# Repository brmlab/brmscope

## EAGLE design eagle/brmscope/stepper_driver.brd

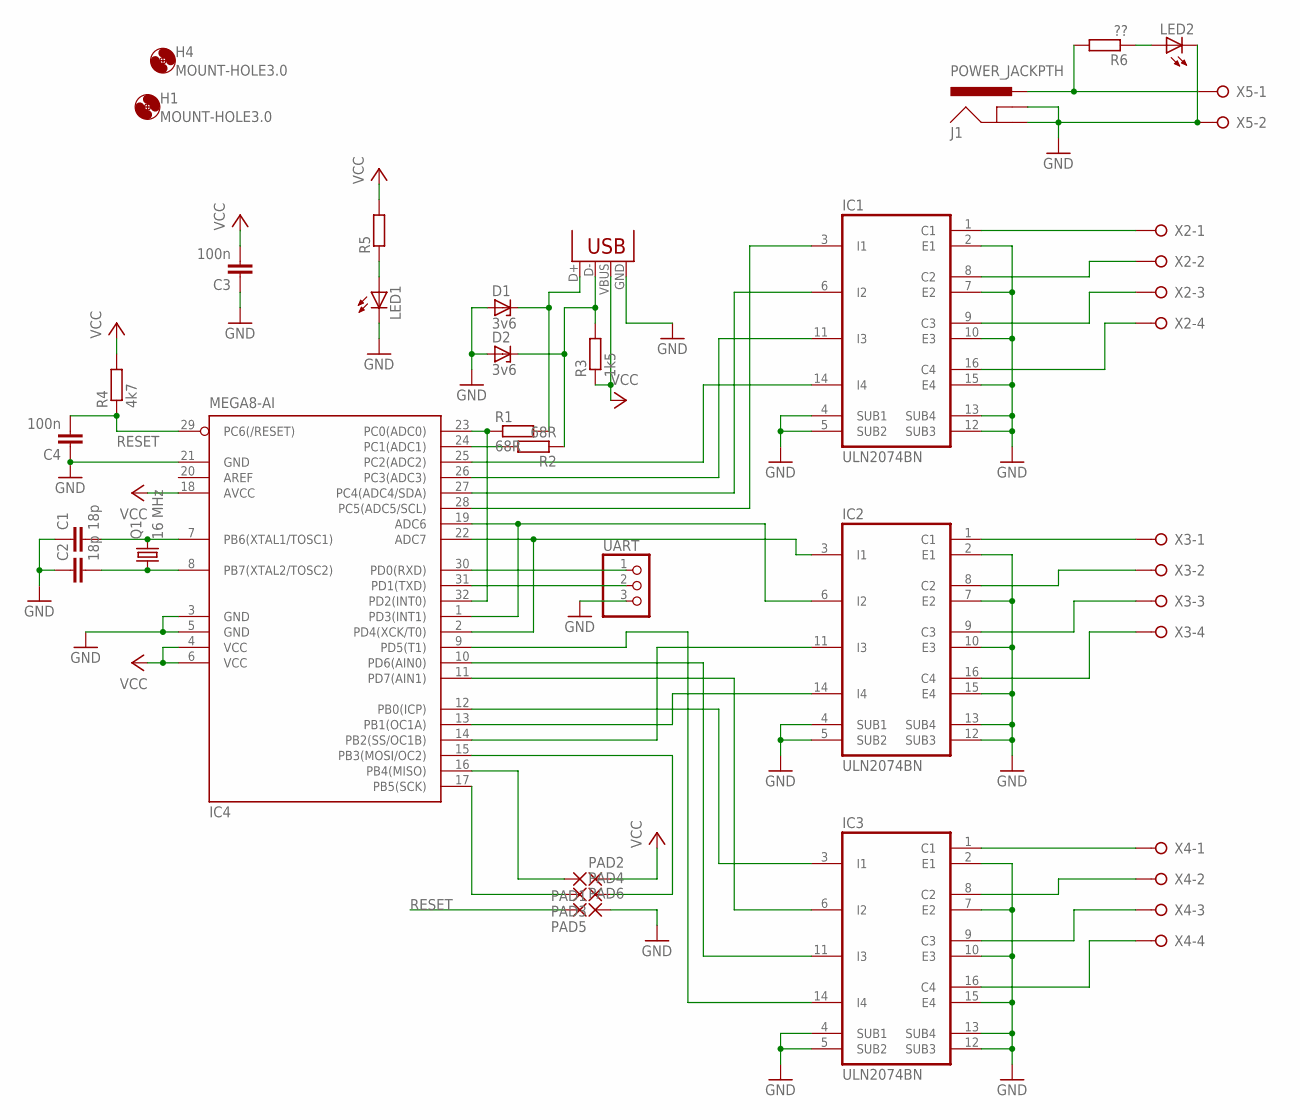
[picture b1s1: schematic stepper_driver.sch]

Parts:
C1, C2: 18p; C025-025X050
C3, C4: 100n; C025-025X050
D1, D2: 3v6; DO35Z10
H1, H4: MOUNT-HOLE3.0; 3,0
IC1, IC2, IC3: ULN2074BN; DIL16
IC4: MEGA8-AI; TQFP32-08
J1: POWER_JACKPTH; POWER_JACK_PTH
LED1, LED2: LED3MM
PAD1, PAD2, PAD3, PAD4, PAD5, PAD6: 2,15/1,0
Q1: 16 MHz; HC49/S
R1, R2: 68R; 0207/10
R3: 1k5; 0207/10
R4: 4k7; 0207/10
R5: R-EU_0207/10; 0207/10
R6: ??; 0207/10
UART: PINHD-1X3; 1X03
X1: USBPTH; USB-B-PTH
X2, X3, X4: W237-04P; W237-4P
X5: W237-02P; W237-132

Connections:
GND: C1.1, C2.1, C3.1, C4.1, D1.A, D2.A, IC1.2 (E1), IC1.4 (SUB1), IC1.5 (SUB2), IC1.7 (E2), IC1.10 (E3), IC1.12 (SUB3), IC1.13 (SUB4), IC1.15 (E4), IC2.2 (E1), IC2.4 (SUB1), IC2.5 (SUB2), IC2.7 (E2), IC2.10 (E3), IC2.12 (SUB3), IC2.13 (SUB4), IC2.15 (E4), IC3.2 (E1), IC3.4 (SUB1), IC3.5 (SUB2), IC3.7 (E2), IC3.10 (E3), IC3.12 (SUB3), IC3.13 (SUB4), IC3.15 (E4), IC4.3 (GND), IC4.5 (GND), IC4.21 (GND), J1.GND, J1.GNDBREAK, LED1.K (C), LED2.K (C), PAD6.1, UART.3, X1.GND, X5.2
unnamed: C2.2, IC4.8 (PB7(XTAL2/TOSC2)), Q1.1
unnamed: C1.2, IC4.7 (PB6(XTAL1/TOSC1)), Q1.2
unnamed: IC4.15 (PB3(MOSI/OC2)), PAD4.1
unnamed: IC4.23 (PC0(ADC0)), IC4.32 (PD2(INT0)), R1.1
unnamed: IC4.24 (PC1(ADC1)), R2.2
unnamed: D1.C, R1.2, X1.D+
unnamed: D2.C, R2.1, R3.2, X1.D-
unnamed: IC1.14 (I4), IC4.25 (PC2(ADC2))
unnamed: IC1.11 (I3), IC4.26 (PC3(ADC3))
unnamed: IC1.6 (I2), IC4.27 (PC4(ADC4/SDA))
unnamed: IC1.3 (I1), IC4.28 (PC5(ADC5/SCL))
unnamed: IC2.6 (I2), IC4.1 (PD3(INT1)), IC4.19 (ADC6)
unnamed: IC2.3 (I1), IC4.2 (PD4(XCK/T0)), IC4.22 (ADC7)
unnamed: IC4.17 (PB5(SCK)), PAD3.1
unnamed: IC4.16 (PB4(MISO)), PAD1.1
unnamed: IC2.11 (I3), IC4.14 (PB2(SS/OC1B))
unnamed: IC2.14 (I4), IC4.13 (PB1(OC1A))
unnamed: IC3.3 (I1), IC4.12 (PB0(ICP))
unnamed: IC3.6 (I2), IC4.11 (PD7(AIN1))
unnamed: IC3.14 (I4), IC4.9 (PD5(T1))
unnamed: IC3.11 (I3), IC4.10 (PD6(AIN0))
unnamed: IC4.30 (PD0(RXD)), UART.1
unnamed: IC4.31 (PD1(TXD)), UART.2
unnamed: IC1.1 (C1), X2.1
unnamed: IC1.8 (C2), X2.2
unnamed: IC1.9 (C3), X2.3
unnamed: IC1.16 (C4), X2.4
unnamed: IC2.1 (C1), X3.1
unnamed: IC2.8 (C2), X3.2
unnamed: IC2.9 (C3), X3.3
unnamed: IC2.16 (C4), X3.4
unnamed: IC3.1 (C1), X4.1
unnamed: IC3.8 (C2), X4.2
unnamed: IC3.9 (C3), X4.3
unnamed: IC3.16 (C4), X4.4
unnamed: LED1.A, R5.1
unnamed: J1.PWR, R6.2, X5.1
unnamed: LED2.A, R6.1
RESET: C4.2, IC4.29 (PC6(/RESET)), PAD5.1, R4.1
VCC: C3.2, IC4.4 (VCC), IC4.6 (VCC), IC4.18 (AVCC), PAD2.1, R3.1, R4.2, R5.2, X1.VBUS

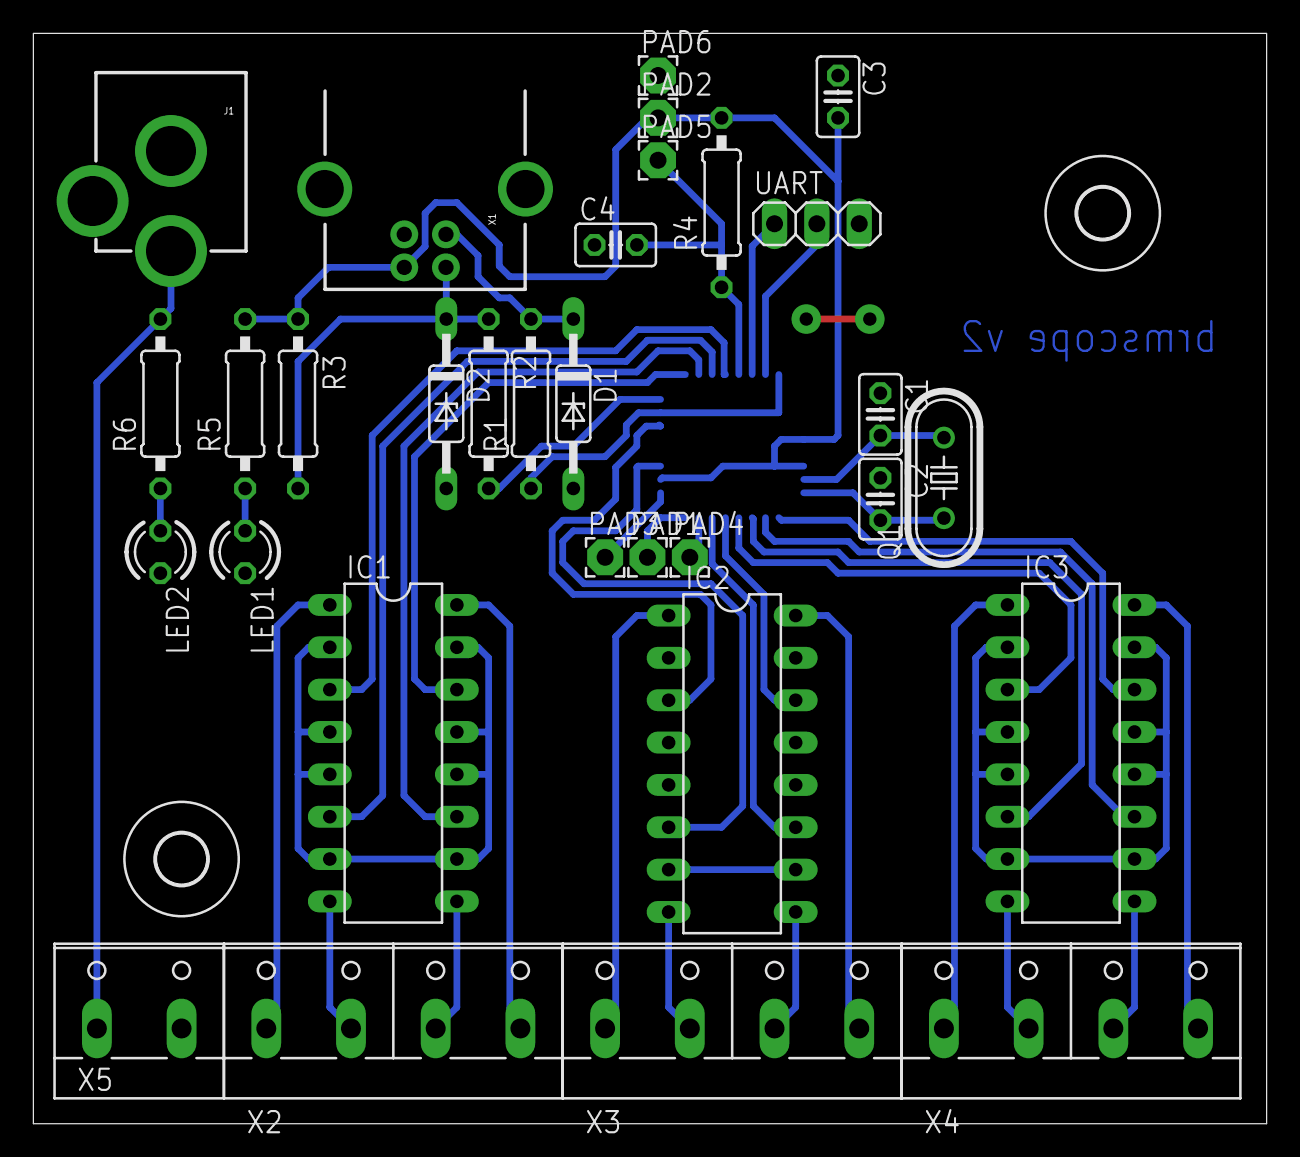
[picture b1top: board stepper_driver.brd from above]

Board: 2 copper layers, 74.0 x 65.4 mm, 34 parts (1 on the bottom side), 41 nets.

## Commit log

2011-08-30 BrmScope INIT COMMIT
2011-08-30 Pridan ARDUINO CODE
2012-09-17 Stepper driver board v2
2012-09-17 .gitignore
2012-09-17 Micropositioner to stepper shaft adapter
2012-09-17 INT0 connected to D+ line (USBasploader requirement)
2012-09-17 Added bootloader code - USBasploader by Objective Development (http://obdev.at/vusb)
2012-09-18 board corrections + atmega firmware
2012-09-18 old code cleanup

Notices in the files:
parts and their libraries:
SparkFun: Licensing: CC v3.0 Share-Alike You are welcome to use this library for commercial purposes.
